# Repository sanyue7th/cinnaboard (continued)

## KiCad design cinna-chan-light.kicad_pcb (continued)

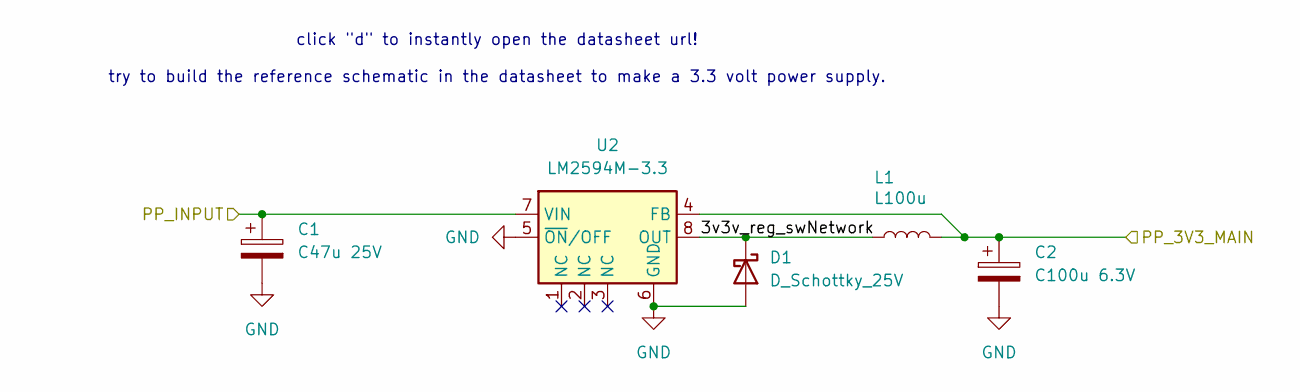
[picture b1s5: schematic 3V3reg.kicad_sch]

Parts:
C1: C47u 25V; C_0201_0603Metric; LCSC C14663
C2: C100u 6.3V; C_0201_0603Metric; LCSC C14663
D1: D_Schottky_25V; D_2114_3652Metric; LCSC C466507
L1: L100u; L_0201_0603Metric; LCSC C162581
U2: LM2594M-3.3; SOIC-8_3.9x4.9mm_P1.27mm; LCSC C316691

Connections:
/3v3: C2.1, L1.2, U2.4 (FB)
/usbcpd/3V3reg/3v3v_reg_swNetwork: D1.1 (K), L1.1, U2.8 (OUT)
/usbcpd/3V3reg/PP_INPUT: C1.1, U2.7 (VIN)
GND: C1.2, C2.2, D1.2 (A), U2.5 (~ON/OFF), U2.6 (GND); also elsewhere on the board

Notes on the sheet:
click "d" to instantly open the datasheet url! try to build the reference schematic in the datasheet to make a 3.3 volt power supply.

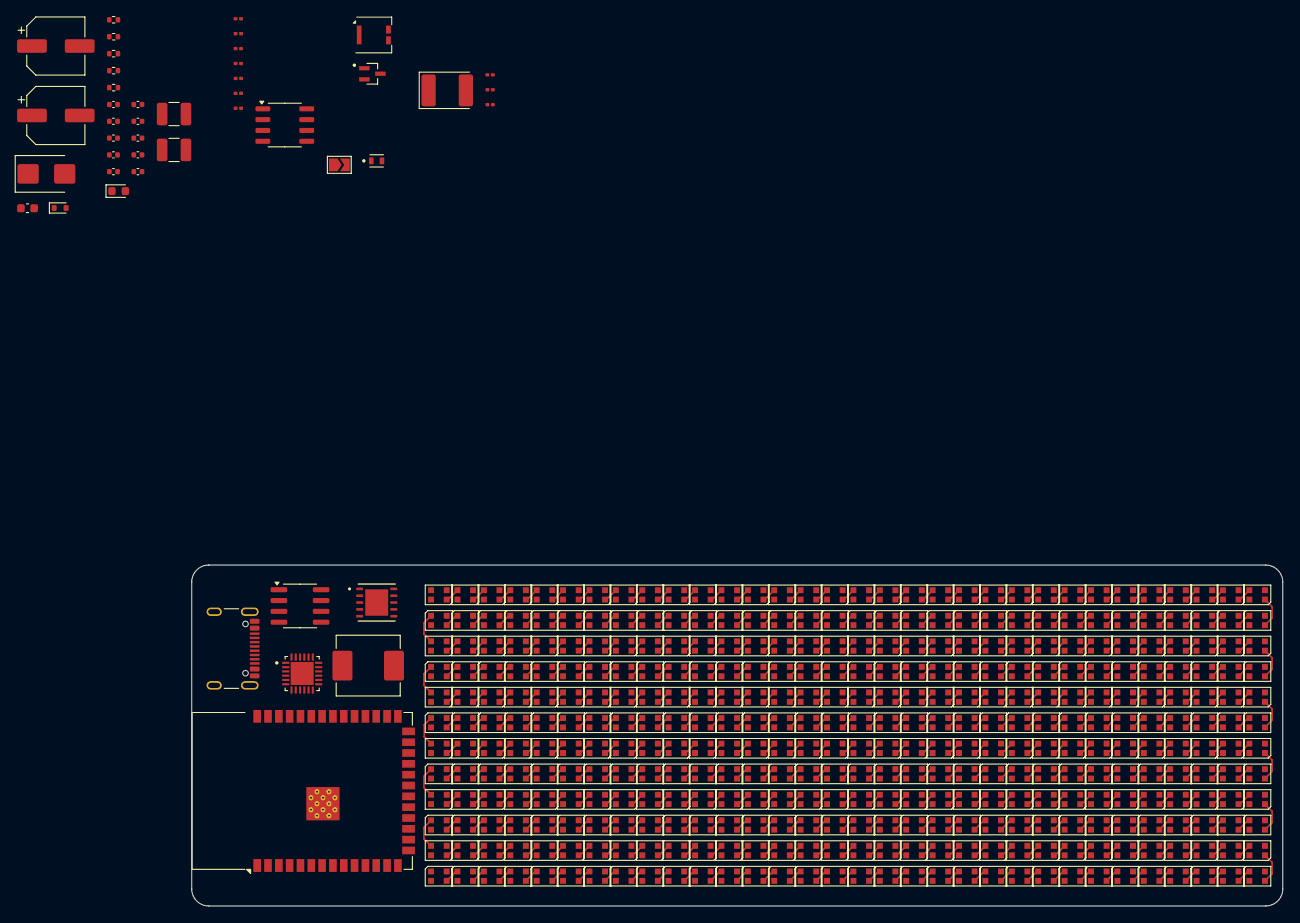
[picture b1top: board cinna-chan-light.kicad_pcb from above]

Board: 2 copper layers, 128.0 x 40.0 mm, 429 parts (0 on the bottom side), 410 nets.

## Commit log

2025-03-06 first commit!!!
2025-03-07 Create power regulator schematic
2025-03-08 Add USBC material
2025-03-10 cinny work!!!!
2025-03-10 Make thing
2025-03-11 Fix mils error
2025-03-21 added lcsc, datasheet, and footprint. couldn't find zener and polarized stuff tho
2025-03-30 Add light-white
2025-04-08 cinna 4 more circuit
2025-04-09 Cleanup, add 5vREG block
2025-04-15 5 volt regulator for PVT
2025-05-04 layout
